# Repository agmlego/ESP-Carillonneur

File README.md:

ESP Carillonneur
================

A project to ESP-ify the "Caroling Christmas Bells" product line from Ye Merrie Minstrel, in particular the variant with part number AUS-200.

## Goals:

* Maintain function with the existing OEM music cartridges
* Allow MIDI control over WiFi
* Allow MIDI control from local storage (SD? Flash?)

## Pinout

### Blue (Right) Bell Connector
0. `IO23` (Furthest from connector)
1. `IO21`
2. `IO18`
3. `IO5`
4. `IO19`
5. `IO22` (Closest to connector)

### Orange (Left) Bell Connector
0. `IO16` (Furthest from connector)
1. `IO4`
2. `IO26`
3. `IO25`
4. `IO27`
5. `IO17` (Closest to connector)

### IR expansion Interface
0. `IO32`
1. `IO34`
2. `IO33`
3. `IO35`

### Mainboard Detection Signals
* "Detect" (on the AUS-200, a 10k pulldown): `IO39`
* "Ref" (on the AUS-200, a 4V reference from resistor divider and IN4148): `IO36`

## Case

The case design uses four M2 heat-set inserts ([94459A120](https://www.mcmaster.com/94459A120/)) and four M2 x 5mm button-head screws ([92095A452]https://www.mcmaster.com/92095A452/). The existing sliding door needs a 1/4" diameter slot cut in the back wall, 1/2" in from the mating edge. This will clear the antenna port.

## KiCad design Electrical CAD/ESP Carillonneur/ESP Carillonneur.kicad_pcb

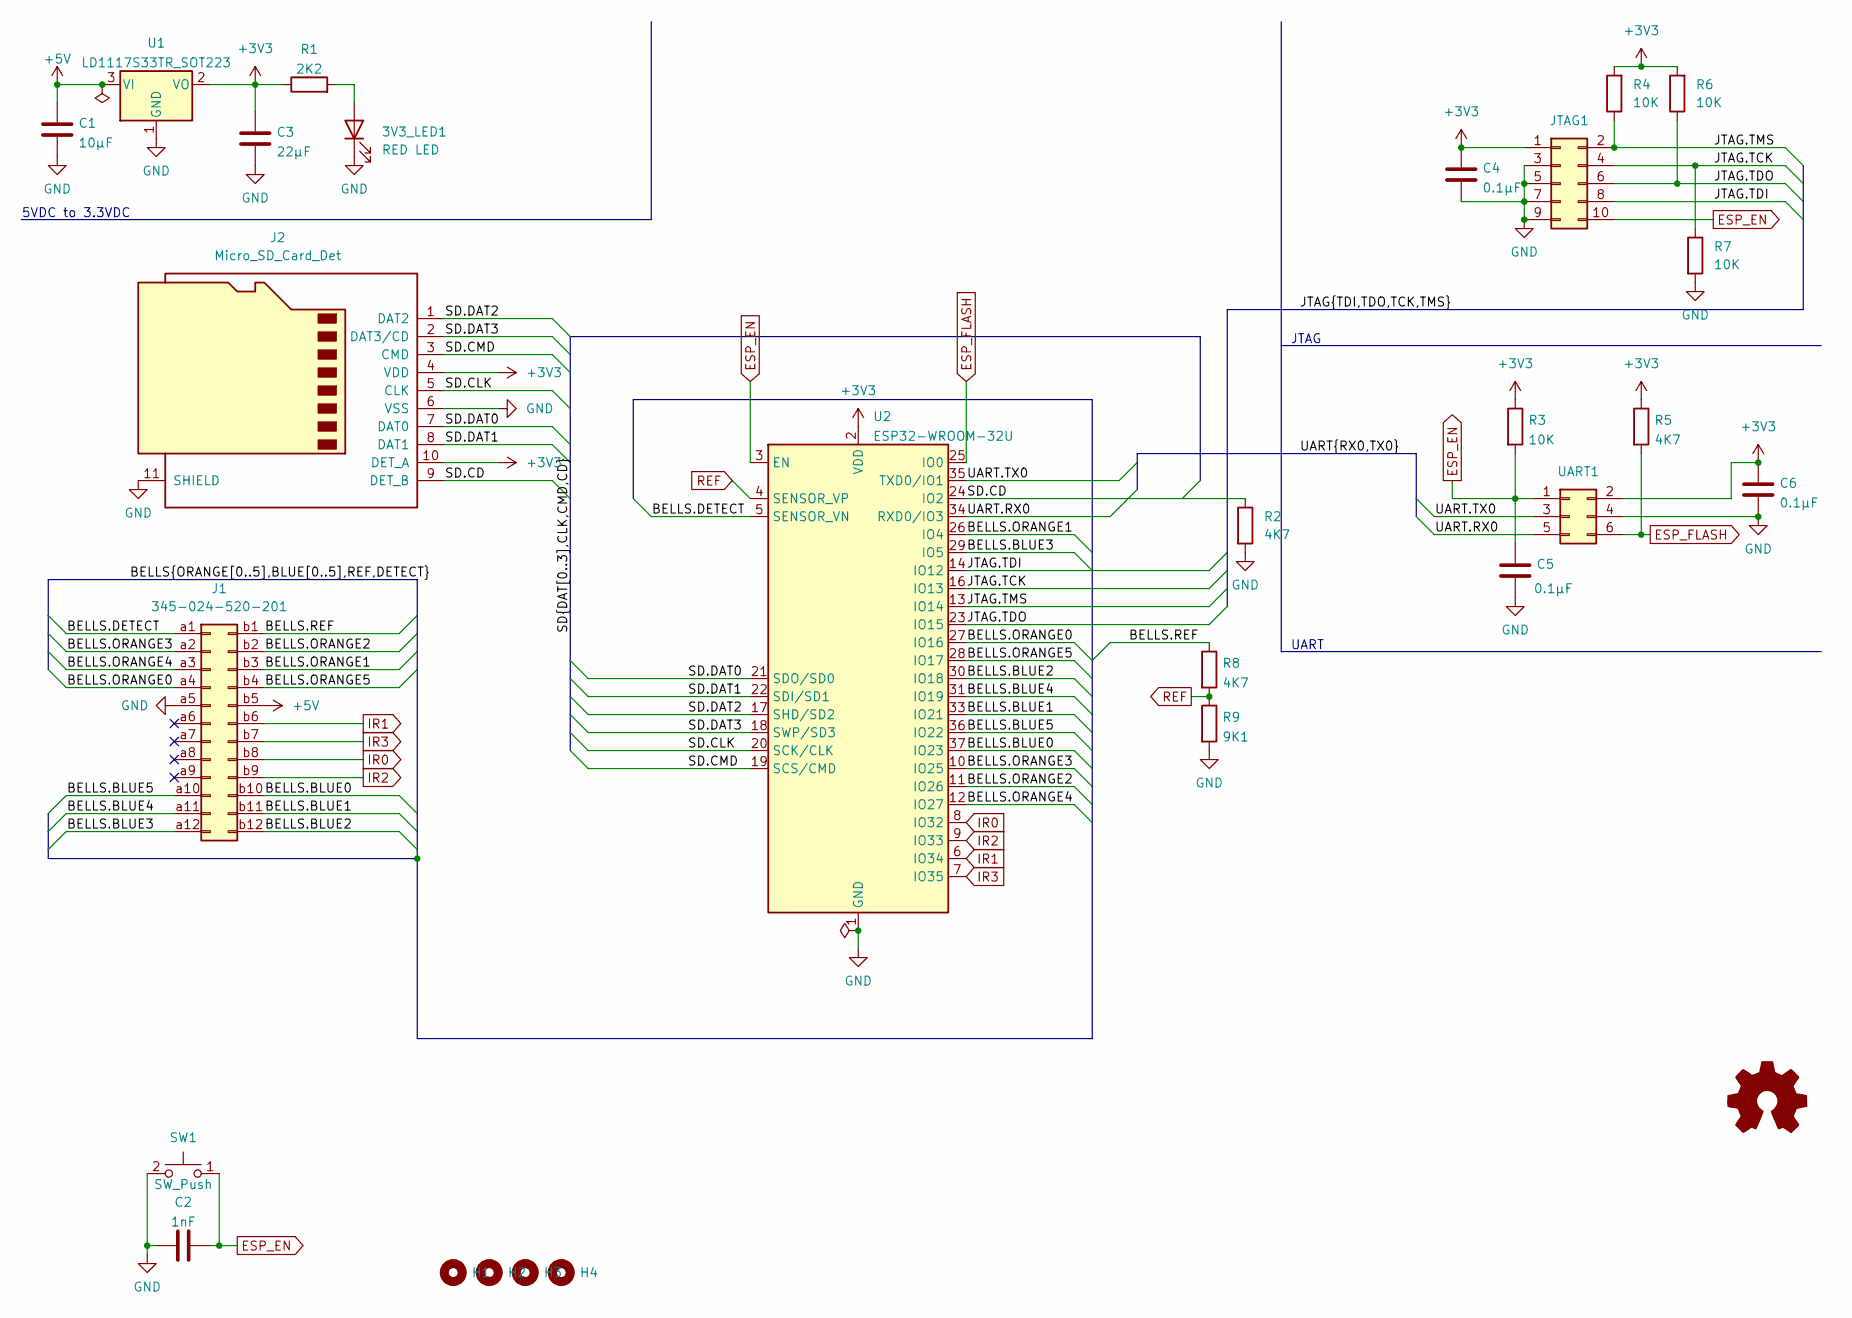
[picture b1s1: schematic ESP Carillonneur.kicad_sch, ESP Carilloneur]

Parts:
3V3_LED1: RED LED; LED_0603_1608Metric
C1: 10µF; CP_Elec_4x4.5
C2: 1nF; C_0603_1608Metric
C3: 22µF; CP_Elec_4x4.5
C4, C5, C6: 0.1µF; C_0603_1608Metric
H1, H2, H3, H4: MountingHole; MountingHole_2.2mm_M2
J1: 345-024-520-201; EEC12DRAN
J2: Micro_SD_Card_Det; microSD_HC_Hirose_DM3AT-SF-PEJM5
JTAG1: Conn_02x05_Odd_Even; Tag-Connect_TC2050-IDC-NL_2x05_P1.27mm_Vertical
R1: 2K2; R_0603_1608Metric
R2, R5, R8: 4K7; R_0603_1608Metric
R3, R4, R6, R7: 10K; R_0603_1608Metric
R9: 9K1; R_0603_1608Metric
SW1: SW_Push; Panasonic_EVQPUL_EVQPUC
U1: LD1117S33TR_SOT223; SOT-223-3_TabPin2
U2: ESP32-WROOM-32U
UART1: Conn_02x03_Odd_Even; Tag-Connect_TC2030-IDC-NL_2x03_P1.27mm_Vertical

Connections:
+3V3: C3.1, C4.1, C6.1, J2.4 (VDD), J2.10 (DET_A), JTAG1.1, R1.1, R3.1, R4.2, R5.1, R6.2, U1.2 (VO), U2.2 (VDD), UART1.2
+5V: C1.1, J1.b5, U1.3 (VI)
/BELLS.BLUE0: J1.b10, U2.37 (IO23)
/BELLS.BLUE1: J1.b11, U2.33 (IO21)
/BELLS.BLUE2: J1.b12, U2.30 (IO18)
/BELLS.BLUE3: J1.a12, U2.29 (IO5)
/BELLS.BLUE4: J1.a11, U2.31 (IO19)
/BELLS.BLUE5: J1.a10, U2.36 (IO22)
/BELLS.DETECT: J1.a1, U2.5 (SENSOR_VN)
/BELLS.ORANGE0: J1.a4, U2.27 (IO16)
/BELLS.ORANGE1: J1.b3, U2.26 (IO4)
/BELLS.ORANGE2: J1.b2, U2.11 (IO26)
/BELLS.ORANGE3: J1.a2, U2.10 (IO25)
/BELLS.ORANGE4: J1.a3, U2.12 (IO27)
/BELLS.ORANGE5: J1.b4, U2.28 (IO17)
/BELLS.REF: J1.b1, R8.1
/JTAG.TCK: JTAG1.4, R7.1, U2.16 (IO13)
/JTAG.TDI: JTAG1.8, U2.14 (IO12)
/JTAG.TDO: JTAG1.6, R6.1, U2.23 (IO15)
/JTAG.TMS: JTAG1.2, R4.1, U2.13 (IO14)
/SD.CD: J2.9 (DET_B), R2.1, U2.24 (IO2)
/SD.CLK: J2.5 (CLK), U2.20 (SCK/CLK)
/SD.CMD: J2.3 (CMD), U2.19 (SCS/CMD)
/SD.DAT0: J2.7 (DAT0), U2.21 (SDO/SD0)
/SD.DAT1: J2.8 (DAT1), U2.22 (SDI/SD1)
/SD.DAT2: J2.1 (DAT2), U2.17 (SHD/SD2)
/SD.DAT3: J2.2 (DAT3/CD), U2.18 (SWP/SD3)
/UART.RX0: U2.34 (RXD0/IO3), UART1.5
/UART.TX0: U2.35 (TXD0/IO1), UART1.3
ESP_EN: C2.2, C5.1, JTAG1.10, R3.2, SW1.1, U2.3 (EN), UART1.1
ESP_FLASH: R5.2, U2.25 (IO0), UART1.6
GND: 3V3_LED1.1 (K), C1.2, C2.1, C3.2, C4.2, C5.2, C6.2, J1.a5, J2.6 (VSS), J2.11 (SHIELD), JTAG1.3, JTAG1.5, JTAG1.7, JTAG1.9, R2.2, R7.2, R9.2, SW1.2, U1.1 (GND), U2.1 (GND), U2.15 (GND), U2.38 (GND), U2.39 (GND), UART1.4
IR0: J1.b8, U2.8 (IO32)
IR1: J1.b6, U2.6 (IO34)
IR2: J1.b9, U2.9 (IO33)
IR3: J1.b7, U2.7 (IO35)
unnamed: 3V3_LED1.2 (A), R1.2
REF: R8.2, R9.1, U2.4 (SENSOR_VP)

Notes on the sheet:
5VDC to 3.3VDC
JTAG
UART

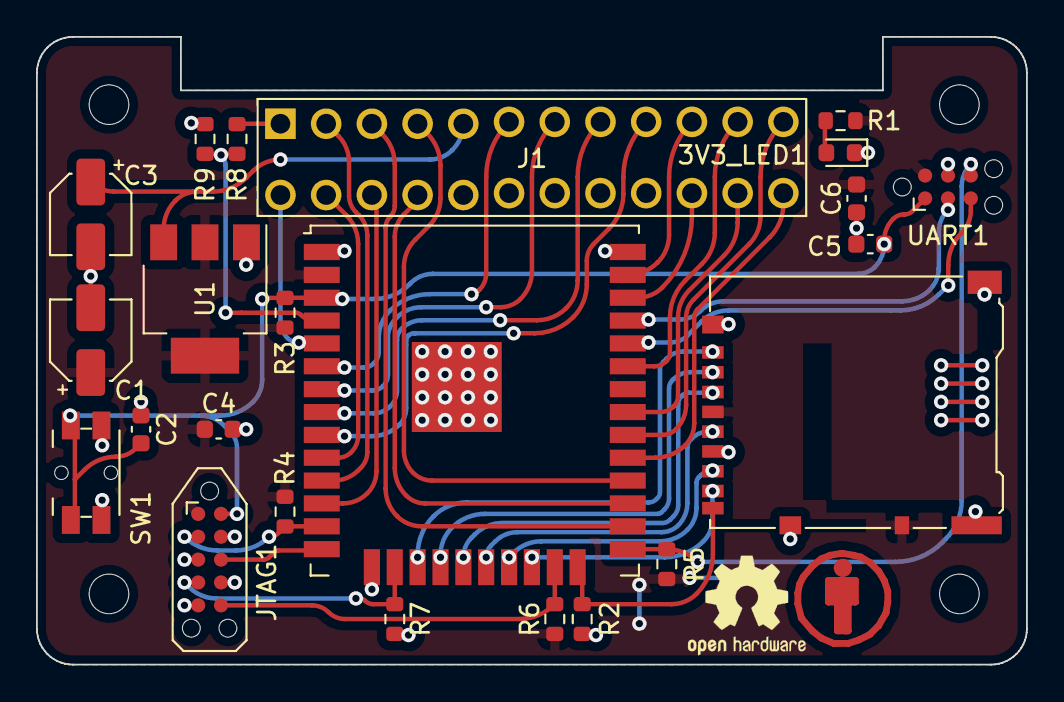
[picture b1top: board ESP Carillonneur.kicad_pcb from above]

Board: 2 copper layers, 55.0 x 34.9 mm, 30 parts (1 on the bottom side), 38 nets.

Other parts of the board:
CC_LOGO: Symbol_CC-Attribution_CopperTop_Small
KiCAD_LOGO: KiCad-Logo2_5mm_SilkScreen
OSHW_LOGO: OSHW-Logo2_7.3x6mm_SilkScreen

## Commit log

2022-12-24 Initial commit
    Reverse-engineering data and schematic, in preparation for ESP cartridge design.
2022-12-24 Rename Mainboard project.
2022-12-24 Schematic design for ESP32-WROOM-32U cartridge
2022-12-24 Changed case because apparently this is not a constant...
2022-12-24 Reworked some pins for better routing; beginning of board art.
2022-12-25 Added voltage divider for BELLS.REF, more routing
2022-12-25 Final bopard routing and silk placement.
2022-12-25 Print readiness and BOMs
2022-12-25 Added pinout to README
2022-12-25 ...formatting is hard.
2023-01-21 Basic start for MIDI
2023-01-21 MIDI works now
2023-01-22 Working bells!!!
2023-01-22 Add initial strike
2023-01-24 First stab at Python sender
    Doesn't actually work, there's library disagreement.
2023-01-27 Revised board to fit existing case
2023-01-27 Changed pinout in README to match new board revision
2023-01-27 Rounded corners, updated BOM
2023-01-27 Ignore Inventor backups.
2023-01-28 Mechanical design for case
2023-01-28 Added notes about case hardware.
2023-01-28 Final case updates.
